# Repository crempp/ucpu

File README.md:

# uCPU

This is a 16bit pipelined CPU designed on a breadboard and produced in modular component boards.

My objective in this project is to learn electronics, CPU design and build a fully functional CPU that can be updated, added to and further developed easily.

The CPU is designed around
* four general purpose 16 bit registers
* four 16 bit address registers
* ALU supporting addition, subtraction, shift and bitwise operations
* piplined instructions
* banked memory with a base of 64k, expandable to about 1.5 megabytes (max TBD)

## Documentation

Documentation is located [here](https://crempp.github.io/ucpu)

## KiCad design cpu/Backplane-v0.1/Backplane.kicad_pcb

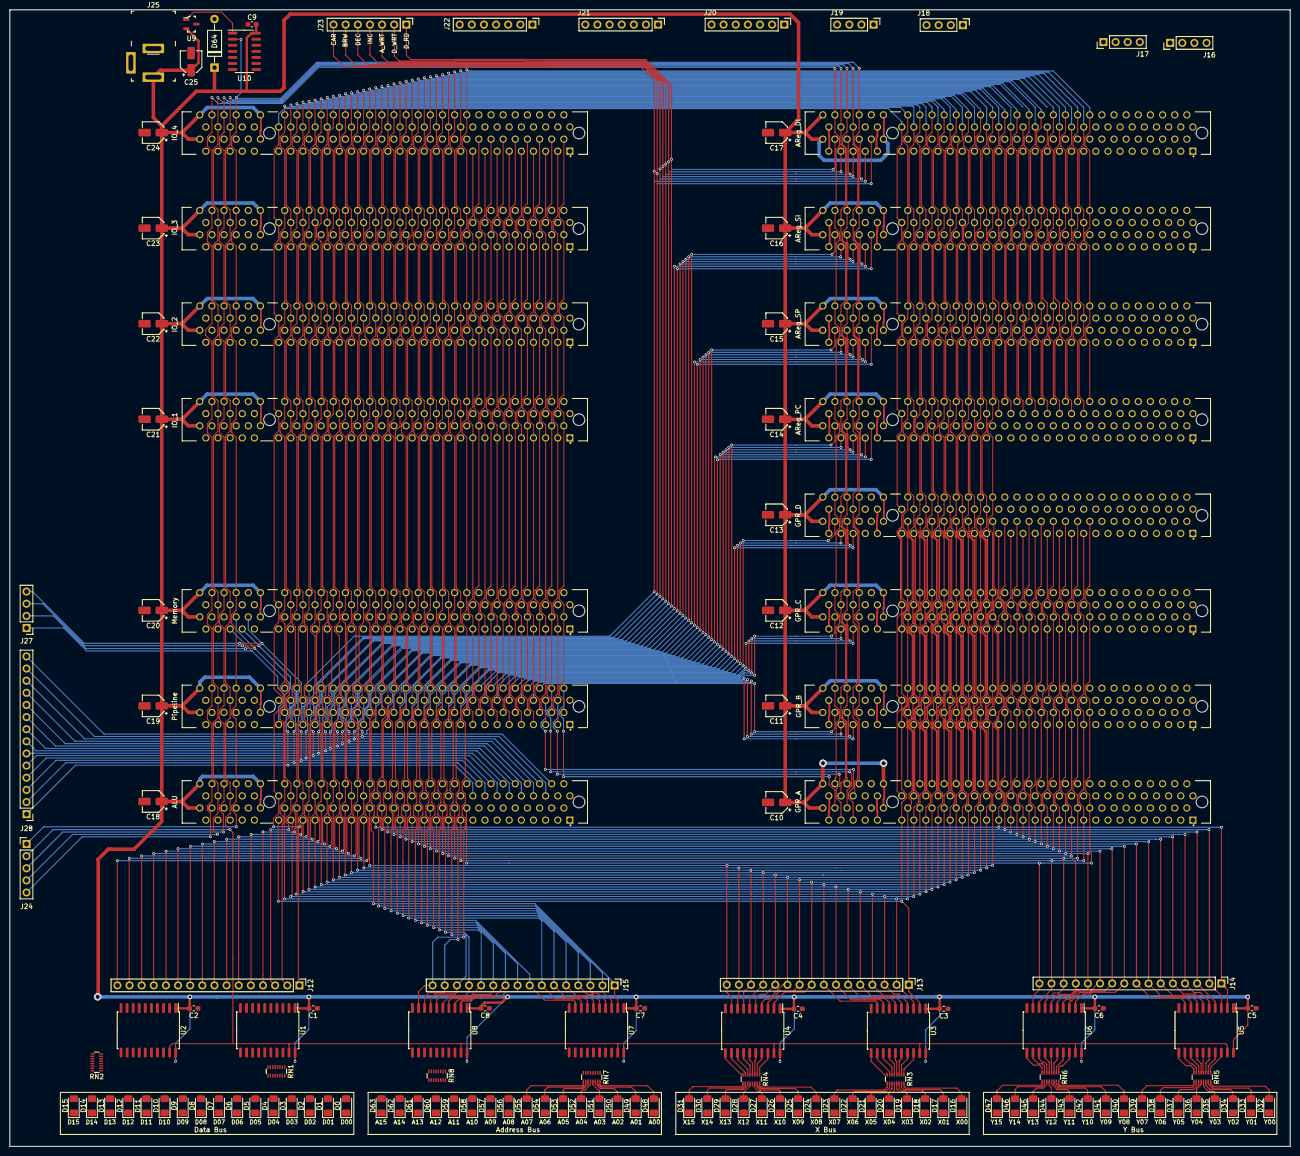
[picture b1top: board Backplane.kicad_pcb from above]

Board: 2 copper layers, 268.0 x 237.9 mm, 139 parts (0 on the bottom side), 278 nets.

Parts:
C1, C2, C3, C4, C5, C6, C7, C8, C9: 0.1uF; C_0603_1608Metric_Pad1.05x0.95mm_HandSolder
C10, C11, C12, C13, C14, C15, C16, C17, C18, C19, C20, C21, C22, C23, C24, C25: 47uF; CP_Elec_4x5.4
D0, D1, D2, D3, D4, D5, D6, D7, D8, D9, D10, D11, D12, D13, D14, D15, D16, D17, D18, D19, D20, D21, D22, D23, D24, D25, D26, D27, D28, D29, D30, D31, D32, D33, D34, D35, D36, D37, D38, D39, D40, D41, D42, D43, D44, D45, D46, D47, D48, D49, D50, D51, D52, D53, D54, D55, D56, D57, D58, D59, D60, D61, D62, D63: LED_BLUE; LED_1206_3216Metric_Pad1.42x1.75mm_HandSolder
D64: D_Zener; D_A-405_P10.16mm_Horizontal
J1: GPR_A; TE_1-5145154-2
J2: GPR_B; TE_1-5145154-2
J3: GPR_C; TE_1-5145154-2
J4: GPR_D; TE_1-5145154-2
J5: AReg_PC; TE_1-5145154-2
J6: AReg_SP; TE_1-5145154-2
J7: AReg_SI; TE_1-5145154-2
J8: AReg_DI; TE_1-5145154-2
J9: Pipeline; TE_1-5145154-2
J10: ALU; TE_1-5145154-2
J11: Memory; TE_1-5145154-2
J12, J13, J14, J15: Conn_01x16_Female; PinHeader_1x16_P2.54mm_Vertical
J16, J17, J18, J19, J27: Conn_01x04_Female; PinHeader_1x04_P2.54mm_Vertical
J20, J21, J22, J23: Conn_01x07_Female; PinHeader_1x07_P2.54mm_Vertical
J24: Conn_01x05_Female; PinHeader_1x05_P2.54mm_Vertical
J25: Barrel_Jack; Barrel_Jack_5.5mmODx2.1mmID_PJ-202A
J28: Conn_01x14_Female; PinHeader_1x14_P2.54mm_Vertical
J29: IO_1; TE_1-5145154-2
J30: IO_2; TE_1-5145154-2
J31: IO_3; TE_1-5145154-2
J32: IO_4; TE_1-5145154-2
RN1, RN2, RN3, RN4, RN5, RN6, RN7, RN8: 220R; R_Array_Convex_8x0602
U1, U2, U3, U4, U5, U6, U7, U8: 74LS245; SOIC-20W_7.5x12.8mm_P1.27mm
U9: MCP100-450D; SOT-23-3
U10: 74LS04; SOIC-14_3.9x8.7mm_P1.27mm

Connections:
+5V: C1.1, C2.1, C3.1, C4.1, C5.1, C6.1, C7.1, C8.1, C9.1, C10.1, C11.1, C12.1, C13.1, C14.1, C15.1, C16.1, C17.1, C18.1, C19.1, C20.1, C21.1, C22.1, C23.1, C24.1, C25.1, D64.1, J1.A52, J1.A62, J1.B52, J1.B62, J2.A52, J2.A62, J2.B52, J2.B62, J3.A52, J3.A62, J3.B52, J3.B62, J4.A52, J4.A62, J4.B52, J4.B62, J5.A52, J5.A62, J5.B52, J5.B62, J6.A52, J6.A62, J6.B52, J6.B62, J7.A52, J7.A62, J7.B52, J7.B62, J8.A52, J8.A62, J8.B52, J8.B62, J9.A52, J9.A62, J9.B52, J9.B62, J10.A52, J10.A62, J10.B52, J10.B62, J11.A52, J11.A62, J11.B52, J11.B62, J25.1, J29.A52, J29.A62, J29.B52, J29.B62, J30.A52, J30.A62, J30.B52, J30.B62, J31.A52, J31.A62, J31.B52, J31.B62, J32.A52, J32.A62, J32.B52, J32.B62, U1.1, U1.20, U2.1, U2.20, U3.1, U3.20, U4.1, U4.20, U5.1, U5.20, U6.1, U6.20, U7.1, U7.20, U8.1, U8.20, U9.2, U10.14
/BANK: J9.A49, J11.A57, J27.1
/CLK: J1.B60, J2.B60, J3.B60, J4.B60, J5.B60, J6.B60, J7.B60, J8.B60, J9.B60, J10.B60, J11.B60, J24.5, J29.B60, J30.B60, J31.B60, J32.B60
/HLT: J1.B58, J2.B58, J3.B58, J4.B58, J5.B58, J6.B58, J7.B58, J8.B58, J9.B58, J10.B58, J11.B58, J24.3, J29.B58, J30.B58, J31.B58, J32.B58
/MEM_RD: J9.A46, J11.A54, J27.4
/MEM_WR: J9.A47, J11.A55, J27.3
/MREQ: J9.A48, J11.A56, J27.2
/RST: J1.B56, J2.B56, J3.B56, J4.B56, J5.B56, J6.B56, J7.B56, J8.B56, J9.B56, J10.B56, J11.B56, J24.1, J29.B56, J30.B56, J31.B56, J32.B56, U10.2
/a_bus_00: J5.B33, J6.B33, J7.B33, J8.B33, J9.B33, J11.B33, J15.1, J29.B33, J30.B33, J31.B33, J32.B33, U7.2
/a_bus_01: J5.B32, J6.B32, J7.B32, J8.B32, J9.B32, J11.B32, J15.2, J29.B32, J30.B32, J31.B32, J32.B32, U7.3
/a_bus_02: J5.B31, J6.B31, J7.B31, J8.B31, J9.B31, J11.B31, J15.3, J29.B31, J30.B31, J31.B31, J32.B31, U7.4
/a_bus_03: J5.B30, J6.B30, J7.B30, J8.B30, J9.B30, J11.B30, J15.4, J29.B30, J30.B30, J31.B30, J32.B30, U7.5
/a_bus_04: J5.B29, J6.B29, J7.B29, J8.B29, J9.B29, J11.B29, J15.5, J29.B29, J30.B29, J31.B29, J32.B29, U7.6
/a_bus_05: J5.B28, J6.B28, J7.B28, J8.B28, J9.B28, J11.B28, J15.6, J29.B28, J30.B28, J31.B28, J32.B28, U7.7
/a_bus_06: J5.B27, J6.B27, J7.B27, J8.B27, J9.B27, J11.B27, J15.7, J29.B27, J30.B27, J31.B27, J32.B27, U7.8
/a_bus_07: J5.B26, J6.B26, J7.B26, J8.B26, J9.B26, J11.B26, J15.8, J29.B26, J30.B26, J31.B26, J32.B26, U7.9
/a_bus_08: J5.B25, J6.B25, J7.B25, J8.B25, J9.B25, J11.B25, J15.9, J29.B25, J30.B25, J31.B25, J32.B25, U8.2
/a_bus_09: J5.B24, J6.B24, J7.B24, J8.B24, J9.B24, J11.B24, J15.10, J29.B24, J30.B24, J31.B24, J32.B24, U8.3
/a_bus_10: J5.B23, J6.B23, J7.B23, J8.B23, J9.B23, J11.B23, J15.11, J29.B23, J30.B23, J31.B23, J32.B23, U8.4
/a_bus_11: J5.B22, J6.B22, J7.B22, J8.B22, J9.B22, J11.B22, J15.12, J29.B22, J30.B22, J31.B22, J32.B22, U8.5
/a_bus_12: J5.B21, J6.B21, J7.B21, J8.B21, J9.B21, J11.B21, J15.13, J29.B21, J30.B21, J31.B21, J32.B21, U8.6
/a_bus_13: J5.B20, J6.B20, J7.B20, J8.B20, J9.B20, J11.B20, J15.14, J29.B20, J30.B20, J31.B20, J32.B20, U8.7
/a_bus_14: J5.B19, J6.B19, J7.B19, J8.B19, J9.B19, J11.B19, J15.15, J29.B19, J30.B19, J31.B19, J32.B19, U8.8
/a_bus_15: J5.B18, J6.B18, J7.B18, J8.B18, J9.B18, J11.B18, J15.16, J29.B18, J30.B18, J31.B18, J32.B18, U8.9
/a_bus_write_di: J8.A58, J9.A41, J23.3
/a_bus_write_pc: J5.A58, J9.A20, J20.3
/a_bus_write_si: J7.A58, J9.A34, J22.3
/a_bus_write_sp: J6.A58, J9.A27, J21.3
/alu_arr_carry_sel_0: J9.B35, J10.B5, J28.13
/alu_arr_carry_sel_1: J9.B34, J10.B4, J28.14
/alu_bit_control_0: J9.B41, J10.B11, J28.7
/alu_bit_control_1: J9.B40, J10.B10, J28.8
/alu_bit_control_2: J9.B39, J10.B9, J28.9
/alu_bit_control_3: J9.B38, J10.B8, J28.10
/alu_shift_control_0: J9.B37, J10.B7, J28.11
/alu_shift_control_1: J9.B36, J10.B6, J28.12
/arrithmetic_carry_flag: J9.B44, J10.B14, J28.4
/d_bus_00: J1.B49, J2.B49, J3.B49, J4.B49, J5.B49, J6.B49, J7.B49, J8.B49, J10.B49, J11.B49, J12.1, J29.B49, J30.B49, J31.B49, J32.B49, U1.2
/d_bus_01: J1.B48, J2.B48, J3.B48, J4.B48, J5.B48, J6.B48, J7.B48, J8.B48, J10.B48, J11.B48, J12.2, J29.B48, J30.B48, J31.B48, J32.B48, U1.3
/d_bus_02: J1.B47, J2.B47, J3.B47, J4.B47, J5.B47, J6.B47, J7.B47, J8.B47, J10.B47, J11.B47, J12.3, J29.B47, J30.B47, J31.B47, J32.B47, U1.4
/d_bus_03: J1.B46, J2.B46, J3.B46, J4.B46, J5.B46, J6.B46, J7.B46, J8.B46, J10.B46, J11.B46, J12.4, J29.B46, J30.B46, J31.B46, J32.B46, U1.5
/d_bus_04: J1.B45, J2.B45, J3.B45, J4.B45, J5.B45, J6.B45, J7.B45, J8.B45, J10.B45, J11.B45, J12.5, J29.B45, J30.B45, J31.B45, J32.B45, U1.6
/d_bus_05: J1.B44, J2.B44, J3.B44, J4.B44, J5.B44, J6.B44, J7.B44, J8.B44, J10.B44, J11.B44, J12.6, J29.B44, J30.B44, J31.B44, J32.B44, U1.7
/d_bus_06: J1.B43, J2.B43, J3.B43, J4.B43, J5.B43, J6.B43, J7.B43, J8.B43, J10.B43, J11.B43, J12.7, J29.B43, J30.B43, J31.B43, J32.B43, U1.8
/d_bus_07: J1.B42, J2.B42, J3.B42, J4.B42, J5.B42, J6.B42, J7.B42, J8.B42, J10.B42, J11.B42, J12.8, J29.B42, J30.B42, J31.B42, J32.B42, U1.9
/d_bus_08: J1.B41, J2.B41, J3.B41, J4.B41, J5.B41, J6.B41, J7.B41, J8.B41, J10.B41, J11.B41, J12.9, J29.B41, J30.B41, J31.B41, J32.B41, U2.2
/d_bus_09: J1.B40, J2.B40, J3.B40, J4.B40, J5.B40, J6.B40, J7.B40, J8.B40, J10.B40, J11.B40, J12.10, J29.B40, J30.B40, J31.B40, J32.B40, U2.3
/d_bus_10: J1.B39, J2.B39, J3.B39, J4.B39, J5.B39, J6.B39, J7.B39, J8.B39, J10.B39, J11.B39, J12.11, J29.B39, J30.B39, J31.B39, J32.B39, U2.4
/d_bus_11: J1.B38, J2.B38, J3.B38, J4.B38, J5.B38, J6.B38, J7.B38, J8.B38, J10.B38, J11.B38, J12.12, J29.B38, J30.B38, J31.B38, J32.B38, U2.5
/d_bus_12: J1.B37, J2.B37, J3.B37, J4.B37, J5.B37, J6.B37, J7.B37, J8.B37, J10.B37, J11.B37, J12.13, J29.B37, J30.B37, J31.B37, J32.B37, U2.6
/d_bus_13: J1.B36, J2.B36, J3.B36, J4.B36, J5.B36, J6.B36, J7.B36, J8.B36, J10.B36, J11.B36, J12.14, J29.B36, J30.B36, J31.B36, J32.B36, U2.7
/d_bus_14: J1.B35, J2.B35, J3.B35, J4.B35, J5.B35, J6.B35, J7.B35, J8.B35, J10.B35, J11.B35, J12.15, J29.B35, J30.B35, J31.B35, J32.B35, U2.8
/d_bus_15: J1.B34, J2.B34, J3.B34, J4.B34, J5.B34, J6.B34, J7.B34, J8.B34, J10.B34, J11.B34, J12.16, J29.B34, J30.B34, J31.B34, J32.B34, U2.9
/d_bus_read_di: J8.A60, J9.A39, J23.1
/d_bus_read_gpr_a: J1.A60, J9.B2, J16.1
/d_bus_read_gpr_b: J2.A60, J9.B6, J17.1
/d_bus_read_gpr_c: J3.A60, J9.B10, J18.1
/d_bus_read_gpr_d: J4.A60, J9.B14, J19.1
/d_bus_read_pc: J5.A60, J9.A18, J20.1
/d_bus_read_si: J7.A60, J9.A32, J22.1
/d_bus_read_sp: J6.A60, J9.A25, J21.1
/d_bus_write_alu: J9.B47, J10.B17, J28.1
/d_bus_write_di: J8.A59, J9.A40, J23.2
/d_bus_write_gpr_a: J1.A59, J9.B3, J16.2
/d_bus_write_gpr_b: J2.A59, J9.B7, J17.2
/d_bus_write_gpr_c: J3.A59, J9.B11, J18.2
/d_bus_write_gpr_d: J4.A59, J9.B15, J19.2
/d_bus_write_pc: J5.A59, J9.A19, J20.2
/d_bus_write_si: J7.A59, J9.A33, J22.2
/d_bus_write_sp: J6.A59, J9.A26, J21.2
/logical_carry_flag: J9.B45, J10.B15, J28.3
/md_bus_00: J9.A17, J11.A17, J29.A17, J30.A17, J31.A17, J32.A17
/md_bus_01: J9.A16, J11.A16, J29.A16, J30.A16, J31.A16, J32.A16
/md_bus_02: J9.A15, J11.A15, J29.A15, J30.A15, J31.A15, J32.A15
/md_bus_03: J9.A14, J11.A14, J29.A14, J30.A14, J31.A14, J32.A14
/md_bus_04: J9.A13, J11.A13, J29.A13, J30.A13, J31.A13, J32.A13
/md_bus_05: J9.A12, J11.A12, J29.A12, J30.A12, J31.A12, J32.A12
/md_bus_06: J9.A11, J11.A11, J29.A11, J30.A11, J31.A11, J32.A11
/md_bus_07: J9.A10, J11.A10, J29.A10, J30.A10, J31.A10, J32.A10
/md_bus_08: J9.A9, J11.A9, J29.A9, J30.A9, J31.A9, J32.A9
/md_bus_09: J9.A8, J11.A8, J29.A8, J30.A8, J31.A8, J32.A8
/md_bus_10: J9.A7, J11.A7, J29.A7, J30.A7, J31.A7, J32.A7
/md_bus_11: J9.A6, J11.A6, J29.A6, J30.A6, J31.A6, J32.A6
/md_bus_12: J9.A5, J11.A5, J29.A5, J30.A5, J31.A5, J32.A5
/md_bus_13: J9.A4, J11.A4, J29.A4, J30.A4, J31.A4, J32.A4
/md_bus_14: J9.A3, J11.A3, J29.A3, J30.A3, J31.A3, J32.A3
/md_bus_15: J9.A2, J11.A2, J29.A2, J30.A2, J31.A2, J32.A2
/overflow_flag: J9.B42, J10.B12, J28.6
/reg_borrow_di: J8.A54, J9.A44, J23.6
/reg_borrow_pc: J5.A54, J9.A23, J20.7
/reg_borrow_si: J7.A54, J9.A37, J22.7
/reg_borrow_sp: J6.A54, J9.A30, J21.7
/reg_carry_di: J8.A55, J9.A45, J23.7
/reg_carry_pc: J5.A55, J9.A24, J20.6
/reg_carry_si: J7.A55, J9.A38, J22.6
/reg_carry_sp: J6.A55, J9.A31, J21.6
/reg_dec_di: J8.A56, J9.A43, J23.5
/reg_dec_pc: J5.A56, J9.A22, J20.5
/reg_dec_si: J7.A56, J9.A36, J22.5
/reg_dec_sp: J6.A56, J9.A29, J21.5
/reg_inc_di: J8.A57, J9.A42, J23.4
/reg_inc_pc: J5.A57, J9.A21, J20.4
/reg_inc_si: J7.A57, J9.A35, J22.4
/reg_inc_sp: J6.A57, J9.A28, J21.4
/sign_flag: J9.B43, J10.B13, J28.5
/x_bus_00: J1.A49, J2.A49, J3.A49, J4.A49, J10.A49, J13.1, U3.2
/x_bus_01: J1.A48, J2.A48, J3.A48, J4.A48, J10.A48, J13.2, U3.3
/x_bus_02: J1.A47, J2.A47, J3.A47, J4.A47, J10.A47, J13.3, U3.4
/x_bus_03: J1.A46, J2.A46, J3.A46, J4.A46, J10.A46, J13.4, U3.5
/x_bus_04: J1.A45, J2.A45, J3.A45, J4.A45, J10.A45, J13.5, U3.6
/x_bus_05: J1.A44, J2.A44, J3.A44, J4.A44, J10.A44, J13.6, U3.7
/x_bus_06: J1.A43, J2.A43, J3.A43, J4.A43, J10.A43, J13.7, U3.8
/x_bus_07: J1.A42, J2.A42, J3.A42, J4.A42, J10.A42, J13.8, U3.9
/x_bus_08: J1.A41, J2.A41, J3.A41, J4.A41, J10.A41, J13.9, U4.2
/x_bus_09: J1.A40, J2.A40, J3.A40, J4.A40, J10.A40, J13.10, U4.3
/x_bus_10: J1.A39, J2.A39, J3.A39, J4.A39, J10.A39, J13.11, U4.4
/x_bus_11: J1.A38, J2.A38, J3.A38, J4.A38, J10.A38, J13.12, U4.5
/x_bus_12: J1.A37, J2.A37, J3.A37, J4.A37, J10.A37, J13.13, U4.6
/x_bus_13: J1.A36, J2.A36, J3.A36, J4.A36, J10.A36, J13.14, U4.7
/x_bus_14: J1.A35, J2.A35, J3.A35, J4.A35, J10.A35, J13.15, U4.8
/x_bus_15: J1.A34, J2.A34, J3.A34, J4.A34, J10.A34, J13.16, U4.9
/x_bus_write_gpr_a: J1.A58, J9.B4, J16.3
/x_bus_write_gpr_b: J2.A58, J9.B8, J17.3
/x_bus_write_gpr_c: J3.A58, J9.B12, J18.3
/x_bus_write_gpr_d: J4.A58, J9.B16, J19.3
/y_bus_00: J1.A33, J2.A33, J3.A33, J4.A33, J10.A33, J14.1, U5.2
/y_bus_01: J1.A32, J2.A32, J3.A32, J4.A32, J10.A32, J14.2, U5.3
/y_bus_02: J1.A31, J2.A31, J3.A31, J4.A31, J10.A31, J14.3, U5.4
/y_bus_03: J1.A30, J2.A30, J3.A30, J4.A30, J10.A30, J14.4, U5.5
/y_bus_04: J1.A29, J2.A29, J3.A29, J4.A29, J10.A29, J14.5, U5.6
/y_bus_05: J1.A28, J2.A28, J3.A28, J4.A28, J10.A28, J14.6, U5.7
/y_bus_06: J1.A27, J2.A27, J3.A27, J4.A27, J10.A27, J14.7, U5.8
/y_bus_07: J1.A26, J2.A26, J3.A26, J4.A26, J10.A26, J14.8, U5.9
/y_bus_08: J1.A25, J2.A25, J3.A25, J4.A25, J10.A25, J14.9, U6.2
/y_bus_09: J1.A24, J2.A24, J3.A24, J4.A24, J10.A24, J14.10, U6.3
/y_bus_10: J1.A23, J2.A23, J3.A23, J4.A23, J10.A23, J14.11, U6.4
/y_bus_11: J1.A22, J2.A22, J3.A22, J4.A22, J10.A22, J14.12, U6.5
/y_bus_12: J1.A21, J2.A21, J3.A21, J4.A21, J10.A21, J14.13, U6.6
/y_bus_13: J1.A20, J2.A20, J3.A20, J4.A20, J10.A20, J14.14, U6.7
/y_bus_14: J1.A19, J2.A19, J3.A19, J4.A19, J10.A19, J14.15, U6.8
/y_bus_15: J1.A18, J2.A18, J3.A18, J4.A18, J10.A18, J14.16, U6.9
/y_bus_write_gpr_a: J1.A57, J9.B5, J16.4
/y_bus_write_gpr_b: J2.A57, J9.B9, J17.4
/y_bus_write_gpr_c: J3.A57, J9.B13, J18.4
/y_bus_write_gpr_d: J4.A57, J9.B17, J19.4
/zero_flag: J9.B46, J10.B16, J28.2
/~CLK: J1.B59, J2.B59, J3.B59, J4.B59, J5.B59, J6.B59, J7.B59, J8.B59, J9.B59, J10.B59, J11.B59, J24.4, J29.B59, J30.B59, J31.B59, J32.B59
/~DBG: J1.B57, J2.B57, J3.B57, J4.B57, J5.B57, J6.B57, J7.B57, J8.B57, J9.B57, J10.B57, J11.B57, J24.2, J29.B57, J30.B57, J31.B57, J32.B57, U1.19, U2.19, U3.19, U4.19, U5.19, U6.19, U7.19, U8.19
GND: C1.2, C2.2, C3.2, C4.2, C5.2, C6.2, C7.2, C8.2, C9.2, C10.2, C11.2, C12.2, C13.2, C14.2, C15.2, C16.2, C17.2, C18.2, C19.2, C20.2, C21.2, C22.2, C23.2, C24.2, C25.2, D0.1, D1.1, D2.1, D3.1, D4.1, D5.1, D6.1, D7.1, D8.1, D9.1, D10.1, D11.1, D12.1, D13.1, D14.1, D15.1, D16.1, D17.1, D18.1, D19.1, D20.1, D21.1, D22.1, D23.1, D24.1, D25.1, D26.1, D27.1, D28.1, D29.1, D30.1, D31.1, D32.1, D33.1, D34.1, D35.1, D36.1, D37.1, D38.1, D39.1, D40.1, D41.1, D42.1, D43.1, D44.1, D45.1, D46.1, D47.1, D48.1, D49.1, D50.1, D51.1, D52.1, D53.1, D54.1, D55.1, D56.1, D57.1, D58.1, D59.1, D60.1, D61.1, D62.1, D63.1, D64.2, J1.A53, J1.A61, J1.B53, J1.B61, J2.A53, J2.A61, J2.B53, J2.B61, J3.A53, J3.A61, J3.B53, J3.B61, J4.A53, J4.A61, J4.B53, J4.B61, J5.A53, J5.A61, J5.B53, J5.B61, J6.A53, J6.A61, J6.B53, J6.B61, J7.A53, J7.A61, J7.B53, J7.B61, J8.A53, J8.A61, J8.B53, J8.B61, J9.A53, J9.A61, J9.B53, J9.B61, J10.A53, J10.A61, J10.B53, J10.B61, J11.A53, J11.A61, J11.B53, J11.B61, J25.2, J29.A53, J29.A61, J29.B53, J29.B61, J30.A53, J30.A61, J30.B53, J30.B61, J31.A53, J31.A61, J31.B53, J31.B61, J32.A53, J32.A61, J32.B53, J32.B61, U1.10, U2.10, U3.10, U4.10, U5.10, U6.10, U7.10, U8.10, U9.3, U10.7
unnamed: D0.2, RN1.16
unnamed: D1.2, RN1.15
unnamed: D2.2, RN1.14
unnamed: D3.2, RN1.13
unnamed: D4.2, RN1.12
unnamed: D5.2, RN1.11
unnamed: D6.2, RN1.10
unnamed: D7.2, RN1.9
unnamed: D8.2, RN2.16
unnamed: D9.2, RN2.15
unnamed: D10.2, RN2.14
unnamed: D11.2, RN2.13
unnamed: D12.2, RN2.12
unnamed: D13.2, RN2.11
unnamed: D14.2, RN2.10
unnamed: D15.2, RN2.9
unnamed: D16.2, RN3.16
unnamed: D17.2, RN3.15
unnamed: D18.2, RN3.14
unnamed: D19.2, RN3.13
unnamed: D20.2, RN3.12
unnamed: D21.2, RN3.11
unnamed: D22.2, RN3.10
unnamed: D23.2, RN3.9
unnamed: D24.2, RN4.16
unnamed: D25.2, RN4.15
unnamed: D26.2, RN4.14
unnamed: D27.2, RN4.13
unnamed: D28.2, RN4.12
unnamed: D29.2, RN4.11
unnamed: D30.2, RN4.10
unnamed: D31.2, RN4.9
unnamed: D32.2, RN5.16
unnamed: D33.2, RN5.15
unnamed: D34.2, RN5.14
unnamed: D35.2, RN5.13
unnamed: D36.2, RN5.12
unnamed: D37.2, RN5.11
unnamed: D38.2, RN5.10
unnamed: D39.2, RN5.9
unnamed: D40.2, RN6.16
unnamed: D41.2, RN6.15
unnamed: D42.2, RN6.14
unnamed: D43.2, RN6.13
unnamed: D44.2, RN6.12
unnamed: D45.2, RN6.11
unnamed: D46.2, RN6.10
unnamed: D47.2, RN6.9
unnamed: D48.2, RN7.16
unnamed: D49.2, RN7.15
unnamed: D50.2, RN7.14
unnamed: D51.2, RN7.13
unnamed: D52.2, RN7.12
unnamed: D53.2, RN7.11
unnamed: D54.2, RN7.10
unnamed: D55.2, RN7.9
unnamed: D56.2, RN8.16
unnamed: D57.2, RN8.15
unnamed: D58.2, RN8.14
unnamed: D59.2, RN8.13
unnamed: D60.2, RN8.12
unnamed: D61.2, RN8.11
unnamed: D62.2, RN8.10
unnamed: D63.2, RN8.9
unnamed: RN1.1, U1.18
unnamed: RN1.2, U1.17
unnamed: RN1.3, U1.16
unnamed: RN1.4, U1.15
unnamed: RN1.5, U1.14
unnamed: RN1.6, U1.13
unnamed: RN1.7, U1.12
unnamed: RN1.8, U1.11
unnamed: RN2.1, U2.18
unnamed: RN2.2, U2.17
unnamed: RN2.3, U2.16
unnamed: RN2.4, U2.15
unnamed: RN2.5, U2.14
unnamed: RN2.6, U2.13
unnamed: RN2.7, U2.12
unnamed: RN2.8, U2.11
unnamed: RN3.1, U3.18
unnamed: RN3.2, U3.17
unnamed: RN3.3, U3.16
unnamed: RN3.4, U3.15
unnamed: RN3.5, U3.14
unnamed: RN3.6, U3.13
unnamed: RN3.7, U3.12
unnamed: RN3.8, U3.11
unnamed: RN4.1, U4.18
unnamed: RN4.2, U4.17
unnamed: RN4.3, U4.16
unnamed: RN4.4, U4.15
unnamed: RN4.5, U4.14
unnamed: RN4.6, U4.13
unnamed: RN4.7, U4.12
unnamed: RN4.8, U4.11
unnamed: RN5.1, U5.18
unnamed: RN5.2, U5.17
unnamed: RN5.3, U5.16
unnamed: RN5.4, U5.15
unnamed: RN5.5, U5.14
unnamed: RN5.6, U5.13
unnamed: RN5.7, U5.12
unnamed: RN5.8, U5.11
unnamed: RN6.1, U6.18
unnamed: RN6.2, U6.17
unnamed: RN6.3, U6.16
unnamed: RN6.4, U6.15
unnamed: RN6.5, U6.14
unnamed: RN6.6, U6.13
unnamed: RN6.7, U6.12
unnamed: RN6.8, U6.11
unnamed: RN7.1, U7.18
unnamed: RN7.2, U7.17
unnamed: RN7.3, U7.16
unnamed: RN7.4, U7.15
unnamed: RN7.5, U7.14
unnamed: RN7.6, U7.13
unnamed: RN7.7, U7.12
unnamed: RN7.8, U7.11
unnamed: RN8.1, U8.18
unnamed: RN8.2, U8.17
unnamed: RN8.3, U8.16
unnamed: RN8.4, U8.15
unnamed: RN8.5, U8.14
unnamed: RN8.6, U8.13
unnamed: RN8.7, U8.12
unnamed: RN8.8, U8.11
unnamed: U9.1, U10.1

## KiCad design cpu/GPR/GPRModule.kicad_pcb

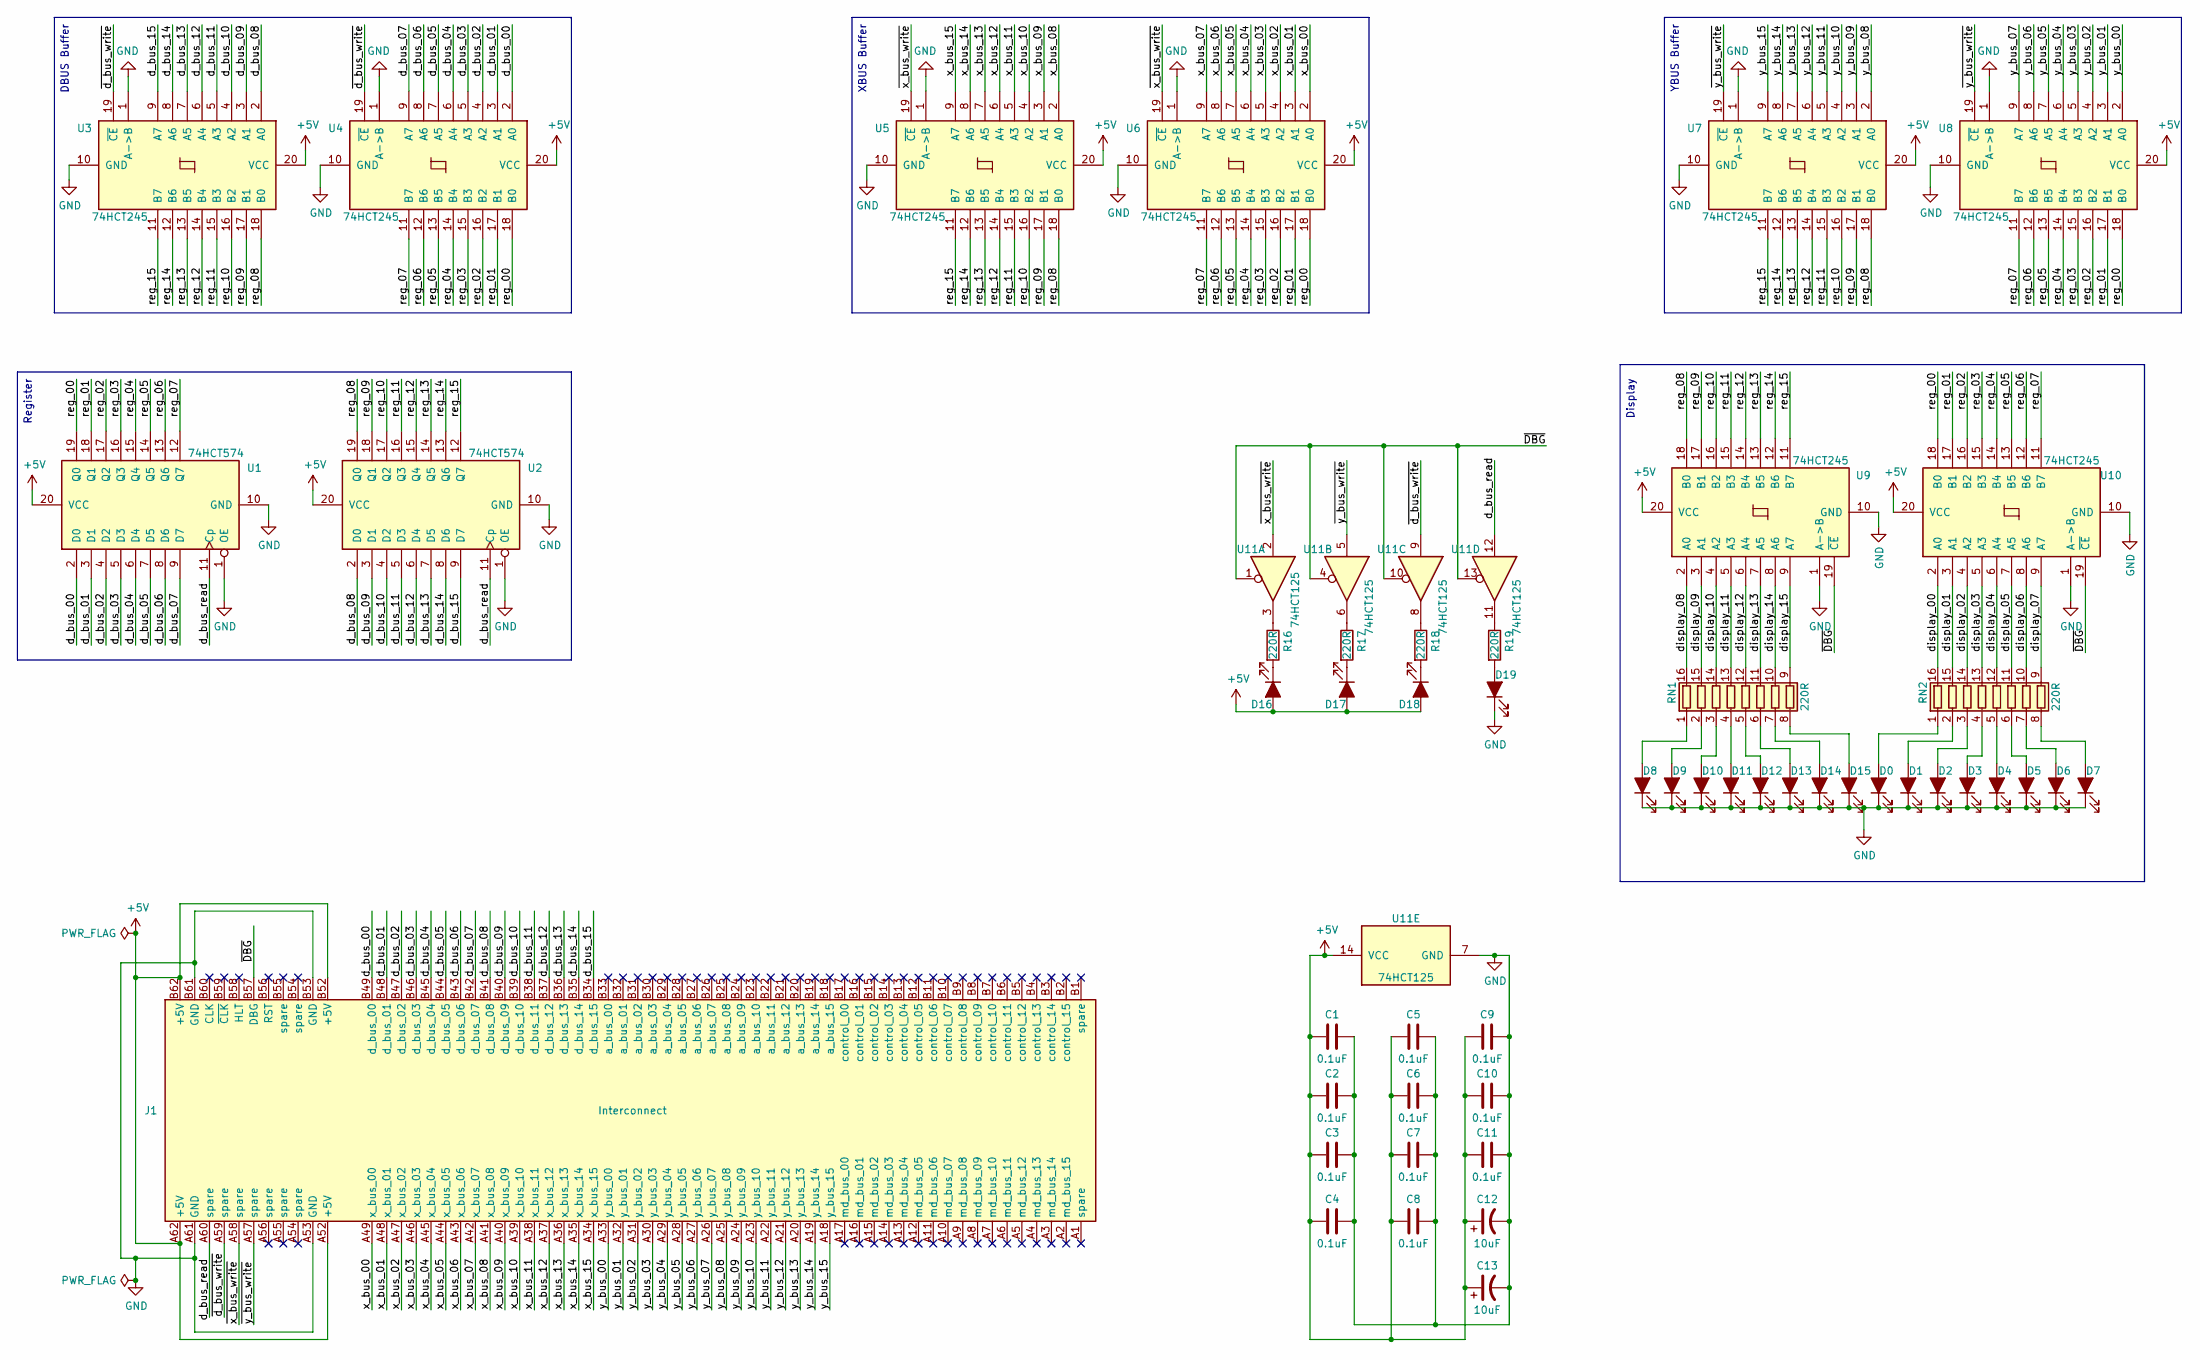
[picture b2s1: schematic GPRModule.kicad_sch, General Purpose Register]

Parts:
C1, C2, C3, C4, C5, C6, C7, C8, C9, C10, C11: 0.1uF; C_0603_1608Metric_Pad1.05x0.95mm_HandSolder; Digikey 399-1096-1-ND
C12, C13: 10uF; CP_Elec_4x5.4; Digikey 493-9786-1-ND
D0, D1, D2, D3, D4, D5, D6, D7, D8, D9, D10, D11, D12, D13, D14, D15: LED_RED; LED_1206_3216Metric_Pad1.42x1.75mm_HandSolder; Digikey 732-4991-1-ND
D16, D17, D18, D19: LED_AMBER; LED_1206_3216Metric_Pad1.42x1.75mm_HandSolder; Digikey 732-4994-1-ND
J1: Interconnect; BUS_PCI
R16, R17, R18, R19: 220R; R_0603_1608Metric_Pad1.05x0.95mm_HandSolder; Digikey 311-220HRCT-ND
RN1, RN2: 220R; R_Array_Convex_8x0602; Digikey Y1221CT-ND
U1, U2: 74HCT574; SOIC-20W_7.5x12.8mm_P1.27mm; Digikey 296-14871-1-ND
U3, U4, U5, U6, U7, U8, U9, U10: 74HCT245; SOIC-20W_7.5x12.8mm_P1.27mm; Digikey 296-1208-1-ND
U11: 74HCT125; SOIC-14_3.9x8.7mm_P1.27mm; Digikey 296-14546-1-ND

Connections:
+5V: C1.2, C2.2, C3.2, C4.2, C5.2, C6.2, C7.2, C8.2, C9.2, C10.2, C11.2, C12.1, C13.1, D16.2 (A), D17.2 (A), D18.2 (A), J1.A52 (+5V), J1.A62 (+5V), J1.B52 (+5V), J1.B62 (+5V), U1.20 (VCC), U2.20 (VCC), U3.20 (VCC), U4.20 (VCC), U5.20 (VCC), U6.20 (VCC), U7.20 (VCC), U8.20 (VCC), U9.20 (VCC), U10.20 (VCC), U11.14 (VCC)
/d_bus_00: J1.B49 (d_bus_00), U1.2 (D0), U4.2 (A0)
/d_bus_01: J1.B48 (d_bus_01), U1.3 (D1), U4.3 (A1)
/d_bus_02: J1.B47 (d_bus_02), U1.4 (D2), U4.4 (A2)
/d_bus_03: J1.B46 (d_bus_03), U1.5 (D3), U4.5 (A3)
/d_bus_04: J1.B45 (d_bus_04), U1.6 (D4), U4.6 (A4)
/d_bus_05: J1.B44 (d_bus_05), U1.7 (D5), U4.7 (A5)
/d_bus_06: J1.B43 (d_bus_06), U1.8 (D6), U4.8 (A6)
/d_bus_07: J1.B42 (d_bus_07), U1.9 (D7), U4.9 (A7)
/d_bus_08: J1.B41 (d_bus_08), U2.2 (D0), U3.2 (A0)
/d_bus_09: J1.B40 (d_bus_09), U2.3 (D1), U3.3 (A1)
/d_bus_10: J1.B39 (d_bus_10), U2.4 (D2), U3.4 (A2)
/d_bus_11: J1.B38 (d_bus_11), U2.5 (D3), U3.5 (A3)
/d_bus_12: J1.B37 (d_bus_12), U2.6 (D4), U3.6 (A4)
/d_bus_13: J1.B36 (d_bus_13), U2.7 (D5), U3.7 (A5)
/d_bus_14: J1.B35 (d_bus_14), U2.8 (D6), U3.8 (A6)
/d_bus_15: J1.B34 (d_bus_15), U2.9 (D7), U3.9 (A7)
/d_bus_read: J1.A60 (spare), U1.11 (Cp), U2.11 (Cp), U11.12
/display_00: RN2.16 (R1.2), U10.2 (A0)
/display_01: RN2.15 (R2.2), U10.3 (A1)
/display_02: RN2.14 (R3.2), U10.4 (A2)
/display_03: RN2.13 (R4.2), U10.5 (A3)
/display_04: RN2.12 (R5.2), U10.6 (A4)
/display_05: RN2.11 (R6.2), U10.7 (A5)
/display_06: RN2.10 (R7.2), U10.8 (A6)
/display_07: RN2.9 (R8.2), U10.9 (A7)
/display_08: RN1.16 (R1.2), U9.2 (A0)
/display_09: RN1.15 (R2.2), U9.3 (A1)
/display_10: RN1.14 (R3.2), U9.4 (A2)
/display_11: RN1.13 (R4.2), U9.5 (A3)
/display_12: RN1.12 (R5.2), U9.6 (A4)
/display_13: RN1.11 (R6.2), U9.7 (A5)
/display_14: RN1.10 (R7.2), U9.8 (A6)
/display_15: RN1.9 (R8.2), U9.9 (A7)
/reg_00: U1.19 (Q0), U4.18 (B0), U6.18 (B0), U8.18 (B0), U10.18 (B0)
/reg_01: U1.18 (Q1), U4.17 (B1), U6.17 (B1), U8.17 (B1), U10.17 (B1)
/reg_02: U1.17 (Q2), U4.16 (B2), U6.16 (B2), U8.16 (B2), U10.16 (B2)
/reg_03: U1.16 (Q3), U4.15 (B3), U6.15 (B3), U8.15 (B3), U10.15 (B3)
/reg_04: U1.15 (Q4), U4.14 (B4), U6.14 (B4), U8.14 (B4), U10.14 (B4)
/reg_05: U1.14 (Q5), U4.13 (B5), U6.13 (B5), U8.13 (B5), U10.13 (B5)
/reg_06: U1.13 (Q6), U4.12 (B6), U6.12 (B6), U8.12 (B6), U10.12 (B6)
/reg_07: U1.12 (Q7), U4.11 (B7), U6.11 (B7), U8.11 (B7), U10.11 (B7)
/reg_08: U2.19 (Q0), U3.18 (B0), U5.18 (B0), U7.18 (B0), U9.18 (B0)
/reg_09: U2.18 (Q1), U3.17 (B1), U5.17 (B1), U7.17 (B1), U9.17 (B1)
/reg_10: U2.17 (Q2), U3.16 (B2), U5.16 (B2), U7.16 (B2), U9.16 (B2)
/reg_11: U2.16 (Q3), U3.15 (B3), U5.15 (B3), U7.15 (B3), U9.15 (B3)
/reg_12: U2.15 (Q4), U3.14 (B4), U5.14 (B4), U7.14 (B4), U9.14 (B4)
/reg_13: U2.14 (Q5), U3.13 (B5), U5.13 (B5), U7.13 (B5), U9.13 (B5)
/reg_14: U2.13 (Q6), U3.12 (B6), U5.12 (B6), U7.12 (B6), U9.12 (B6)
/reg_15: U2.12 (Q7), U3.11 (B7), U5.11 (B7), U7.11 (B7), U9.11 (B7)
/x_bus_00: J1.A49 (x_bus_00), U6.2 (A0)
/x_bus_01: J1.A48 (x_bus_01), U6.3 (A1)
/x_bus_02: J1.A47 (x_bus_02), U6.4 (A2)
/x_bus_03: J1.A46 (x_bus_03), U6.5 (A3)
/x_bus_04: J1.A45 (x_bus_04), U6.6 (A4)
/x_bus_05: J1.A44 (x_bus_05), U6.7 (A5)
/x_bus_06: J1.A43 (x_bus_06), U6.8 (A6)
/x_bus_07: J1.A42 (x_bus_07), U6.9 (A7)
/x_bus_08: J1.A41 (x_bus_08), U5.2 (A0)
/x_bus_09: J1.A40 (x_bus_09), U5.3 (A1)
/x_bus_10: J1.A39 (x_bus_10), U5.4 (A2)
/x_bus_11: J1.A38 (x_bus_11), U5.5 (A3)
/x_bus_12: J1.A37 (x_bus_12), U5.6 (A4)
/x_bus_13: J1.A36 (x_bus_13), U5.7 (A5)
/x_bus_14: J1.A35 (x_bus_14), U5.8 (A6)
/x_bus_15: J1.A34 (x_bus_15), U5.9 (A7)
/y_bus_00: J1.A33 (y_bus_00), U8.2 (A0)
/y_bus_01: J1.A32 (y_bus_01), U8.3 (A1)
/y_bus_02: J1.A31 (y_bus_02), U8.4 (A2)
/y_bus_03: J1.A30 (y_bus_03), U8.5 (A3)
/y_bus_04: J1.A29 (y_bus_04), U8.6 (A4)
/y_bus_05: J1.A28 (y_bus_05), U8.7 (A5)
/y_bus_06: J1.A27 (y_bus_06), U8.8 (A6)
/y_bus_07: J1.A26 (y_bus_07), U8.9 (A7)
/y_bus_08: J1.A25 (y_bus_08), U7.2 (A0)
/y_bus_09: J1.A24 (y_bus_09), U7.3 (A1)
/y_bus_10: J1.A23 (y_bus_10), U7.4 (A2)
/y_bus_11: J1.A22 (y_bus_11), U7.5 (A3)
/y_bus_12: J1.A21 (y_bus_12), U7.6 (A4)
/y_bus_13: J1.A20 (y_bus_13), U7.7 (A5)
/y_bus_14: J1.A19 (y_bus_14), U7.8 (A6)
/y_bus_15: J1.A18 (y_bus_15), U7.9 (A7)
/~DBG: J1.B57 (DBG), U9.19 (~CE), U10.19 (~CE), U11.1, U11.4, U11.10, U11.13
/~d_bus_write: J1.A59 (spare), U3.19 (~CE), U4.19 (~CE), U11.9
/~x_bus_write: J1.A58 (spare), U5.19 (~CE), U6.19 (~CE), U11.2
/~y_bus_write: J1.A57 (spare), U7.19 (~CE), U8.19 (~CE), U11.5
GND: C1.1, C2.1, C3.1, C4.1, C5.1, C6.1, C7.1, C8.1, C9.1, C10.1, C11.1, C12.2, C13.2, D0.1 (K), D1.1 (K), D2.1 (K), D3.1 (K), D4.1 (K), D5.1 (K), D6.1 (K), D7.1 (K), D8.1 (K), D9.1 (K), D10.1 (K), D11.1 (K), D12.1 (K), D13.1 (K), D14.1 (K), D15.1 (K), D19.1 (K), J1.A53 (GND), J1.A61 (GND), J1.B53 (GND), J1.B61 (GND), U1.1 (OE), U1.10 (GND), U2.1 (OE), U2.10 (GND), U3.1 (A->B), U3.10 (GND), U4.1 (A->B), U4.10 (GND), U5.1 (A->B), U5.10 (GND), U6.1 (A->B), U6.10 (GND), U7.1 (A->B), U7.10 (GND), U8.1 (A->B), U8.10 (GND), U9.1 (A->B), U9.10 (GND), U10.1 (A->B), U10.10 (GND), U11.7 (GND)
unnamed: D0.2 (A), RN2.1 (R1.1)
unnamed: D1.2 (A), RN2.2 (R2.1)
unnamed: D2.2 (A), RN2.3 (R3.1)
unnamed: D3.2 (A), RN2.4 (R4.1)
unnamed: D4.2 (A), RN2.5 (R5.1)
unnamed: D5.2 (A), RN2.6 (R6.1)
unnamed: D6.2 (A), RN2.7 (R7.1)
unnamed: D7.2 (A), RN2.8 (R8.1)
unnamed: D8.2 (A), RN1.1 (R1.1)
unnamed: D9.2 (A), RN1.2 (R2.1)
unnamed: D10.2 (A), RN1.3 (R3.1)
unnamed: D11.2 (A), RN1.4 (R4.1)
unnamed: D12.2 (A), RN1.5 (R5.1)
unnamed: D13.2 (A), RN1.6 (R6.1)
unnamed: D14.2 (A), RN1.7 (R7.1)
unnamed: D15.2 (A), RN1.8 (R8.1)
unnamed: D16.1 (K), R16.2
unnamed: D17.1 (K), R17.2
unnamed: D18.1 (K), R18.2
unnamed: D19.2 (A), R19.2
unnamed: R16.1, U11.3
unnamed: R17.1, U11.6
unnamed: R18.1, U11.8
unnamed: R19.1, U11.11

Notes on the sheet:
YBUS Buffer
Register
XBUS Buffer
DBUS Buffer
Display

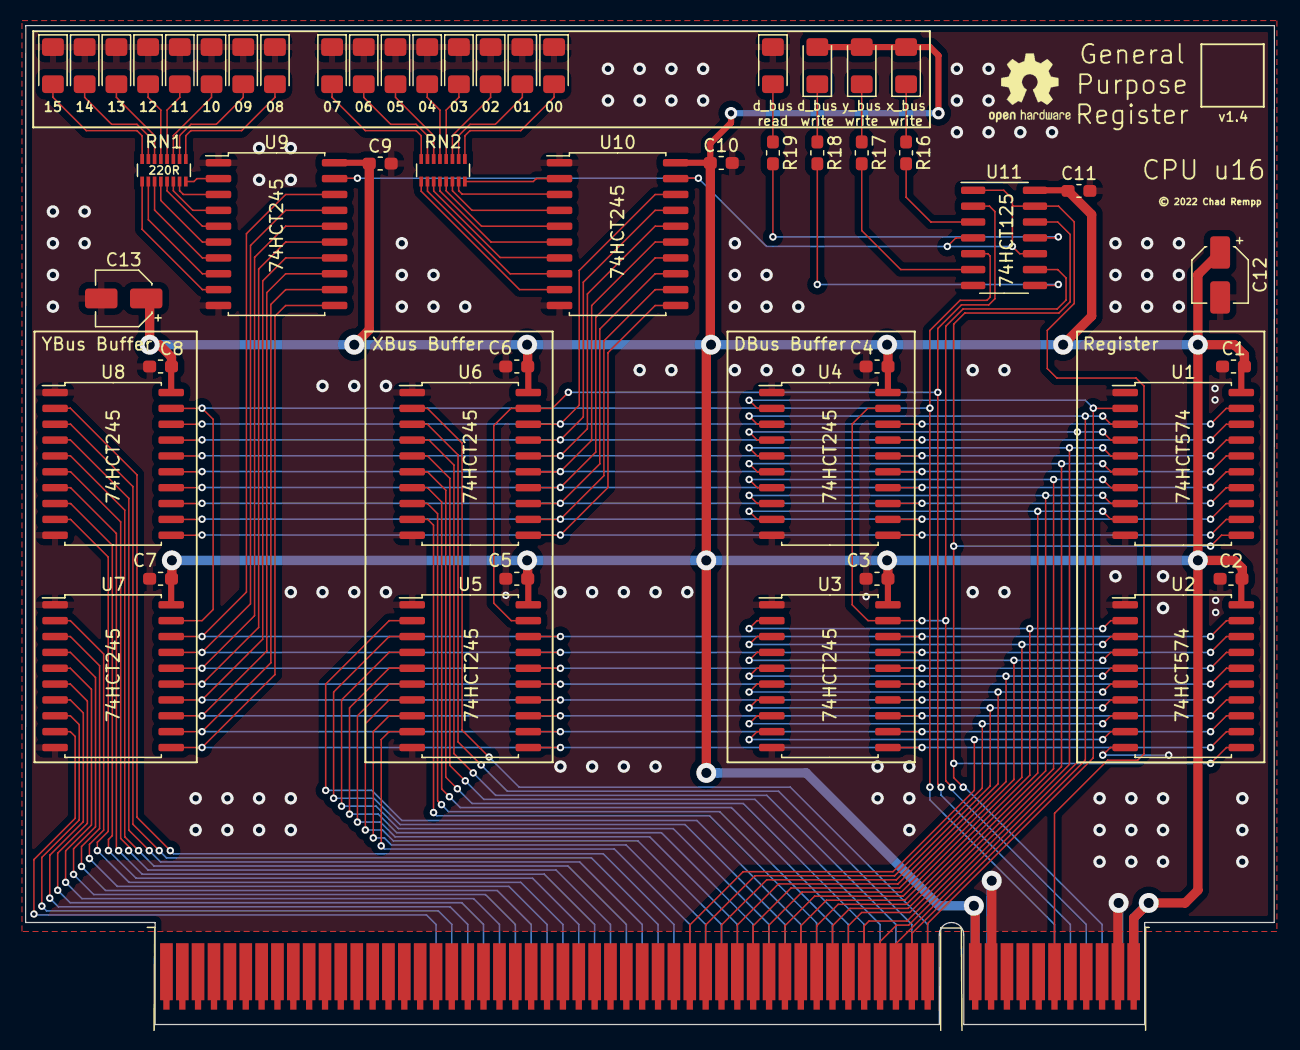
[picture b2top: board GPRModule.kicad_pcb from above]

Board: 2 copper layers, 100.0 x 80.0 mm, 51 parts (0 on the bottom side), 111 nets.

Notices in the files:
cpu/AddressRegister/AddressRegisterModule.kicad_pcb:
© 2022 Chad Rempp
cpu/BreakOutBoard/BreakOutBoard.kicad_pcb:
© 2020 Chad Rempp
